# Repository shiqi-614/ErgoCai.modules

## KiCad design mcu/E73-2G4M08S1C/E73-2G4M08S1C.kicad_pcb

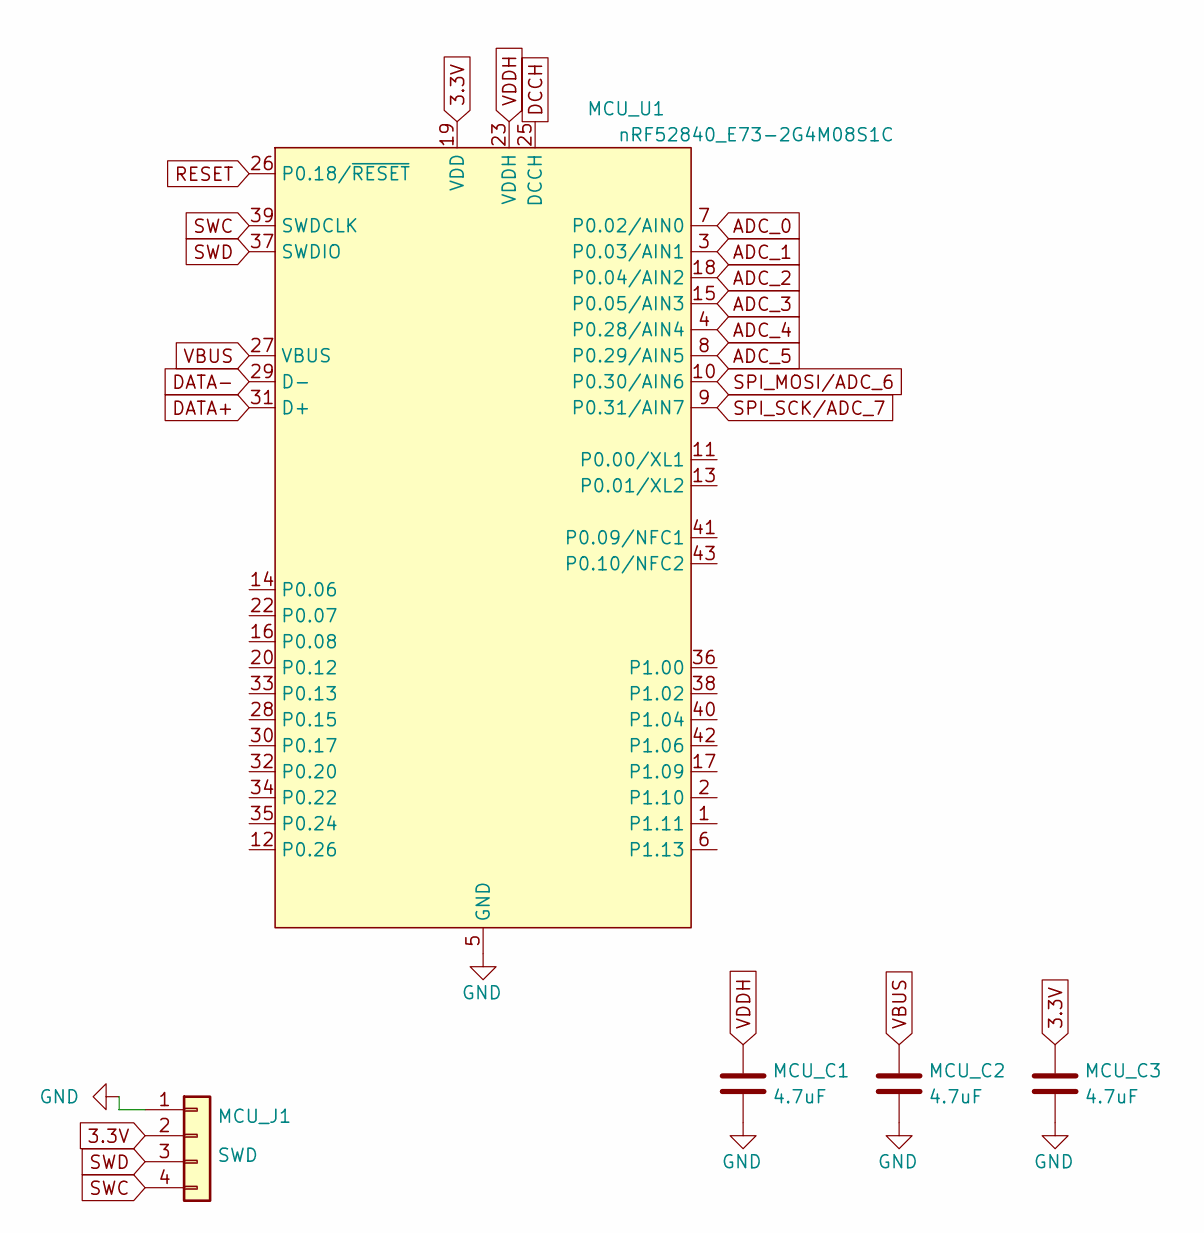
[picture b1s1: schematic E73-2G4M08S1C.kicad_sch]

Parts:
MCU_C1, MCU_C2, MCU_C3: 4.7uF; C_0603_1608Metric
MCU_J1: SWD; Connector_THT_1x4_2.54
MCU_U1: nRF52840_E73-2G4M08S1C; LCSC C356849

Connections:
3.3V: MCU_C3.1, MCU_J1.2, MCU_U1.19 (VDD)
ADC_0: MCU_U1.7 (P0.02/AIN0)
ADC_1: MCU_U1.3 (P0.03/AIN1)
ADC_2: MCU_U1.18 (P0.04/AIN2)
ADC_3: MCU_U1.15 (P0.05/AIN3)
ADC_4: MCU_U1.4 (P0.28/AIN4)
ADC_5: MCU_U1.8 (P0.29/AIN5)
DATA+: MCU_U1.31 (D+)
DATA-: MCU_U1.29 (D-)
DCCH: MCU_U1.25 (DCCH)
GND: MCU_C1.2, MCU_C2.2, MCU_C3.2, MCU_J1.1, MCU_U1.5 (GND), MCU_U1.21 (GND), MCU_U1.24 (GND)
RESET: MCU_U1.26 (P0.18/~RESET)
SPI_MOSI/ADC_6: MCU_U1.10 (P0.30/AIN6)
SPI_SCK/ADC_7: MCU_U1.9 (P0.31/AIN7)
SWC: MCU_J1.4, MCU_U1.39 (SWDCLK)
SWD: MCU_J1.3, MCU_U1.37 (SWDIO)
VBUS: MCU_C2.1, MCU_U1.27 (VBUS)
VDDH: MCU_C1.1, MCU_U1.23 (VDDH)

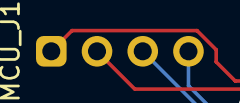
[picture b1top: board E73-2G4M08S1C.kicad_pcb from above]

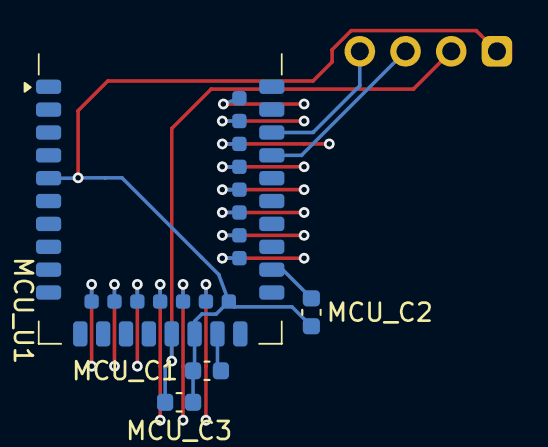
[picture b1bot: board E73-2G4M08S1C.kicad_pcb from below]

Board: 2 copper layers, 5 parts (4 on the bottom side), 6 nets.

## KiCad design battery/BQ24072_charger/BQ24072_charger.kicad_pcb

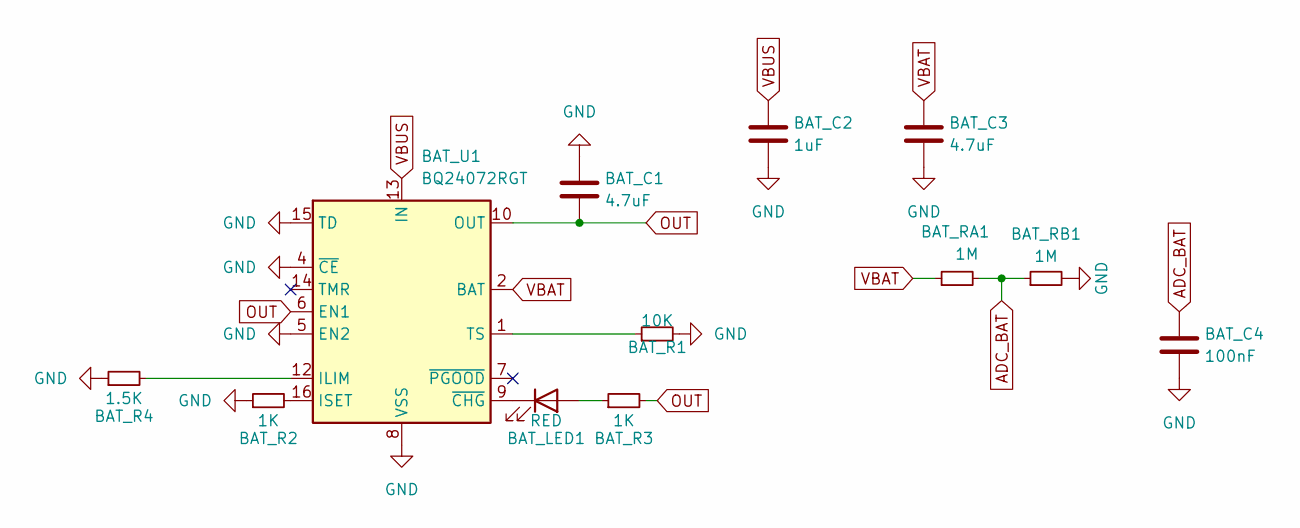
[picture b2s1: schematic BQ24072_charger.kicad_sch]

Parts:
BAT_C1, BAT_C3: 4.7uF; C_0603_1608Metric
BAT_C2: 1uF; C_0603_1608Metric
BAT_C4: 100nF; C_0603_1608Metric
BAT_LED1: RED; LED_0603_1608Metric
BAT_R1: 10K; R_0603_1608Metric
BAT_R2, BAT_R3: 1K; R_0603_1608Metric
BAT_R4: 1.5K; R_0603_1608Metric
BAT_RA1: 1M; R_0603_1608Metric
BAT_RB1: 1M; R_0603_1608Metric
BAT_U1: BQ24072RGT; QFN-16_L3.0-W3.0-P0.50-TL-EP

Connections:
ADC_BAT: BAT_C4.1, BAT_RA1.2, BAT_RB1.1
GND: BAT_C1.1, BAT_C2.2, BAT_C3.2, BAT_C4.2, BAT_R1.2, BAT_R2.1, BAT_R4.1, BAT_RB1.2, BAT_U1.4 (~CE), BAT_U1.5 (EN2), BAT_U1.8 (VSS), BAT_U1.15 (TD), BAT_U1.17 (VSS)
unnamed: BAT_LED1.2 (A), BAT_R3.1
unnamed: BAT_LED1.1 (K), BAT_U1.9 (~CHG)
unnamed: BAT_R4.2, BAT_U1.12 (ILIM)
unnamed: BAT_R2.2, BAT_U1.16 (ISET)
unnamed: BAT_R1.1, BAT_U1.1 (TS)
OUT: BAT_C1.2, BAT_R3.2, BAT_U1.6 (EN1), BAT_U1.10 (OUT), BAT_U1.11 (OUT)
VBAT: BAT_C3.1, BAT_RA1.1, BAT_U1.2 (BAT), BAT_U1.3 (BAT)
VBUS: BAT_C2.1, BAT_U1.13 (IN)

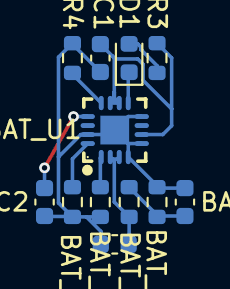
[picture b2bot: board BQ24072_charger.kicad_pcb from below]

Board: 2 copper layers, 12 parts (12 on the bottom side), 10 nets.

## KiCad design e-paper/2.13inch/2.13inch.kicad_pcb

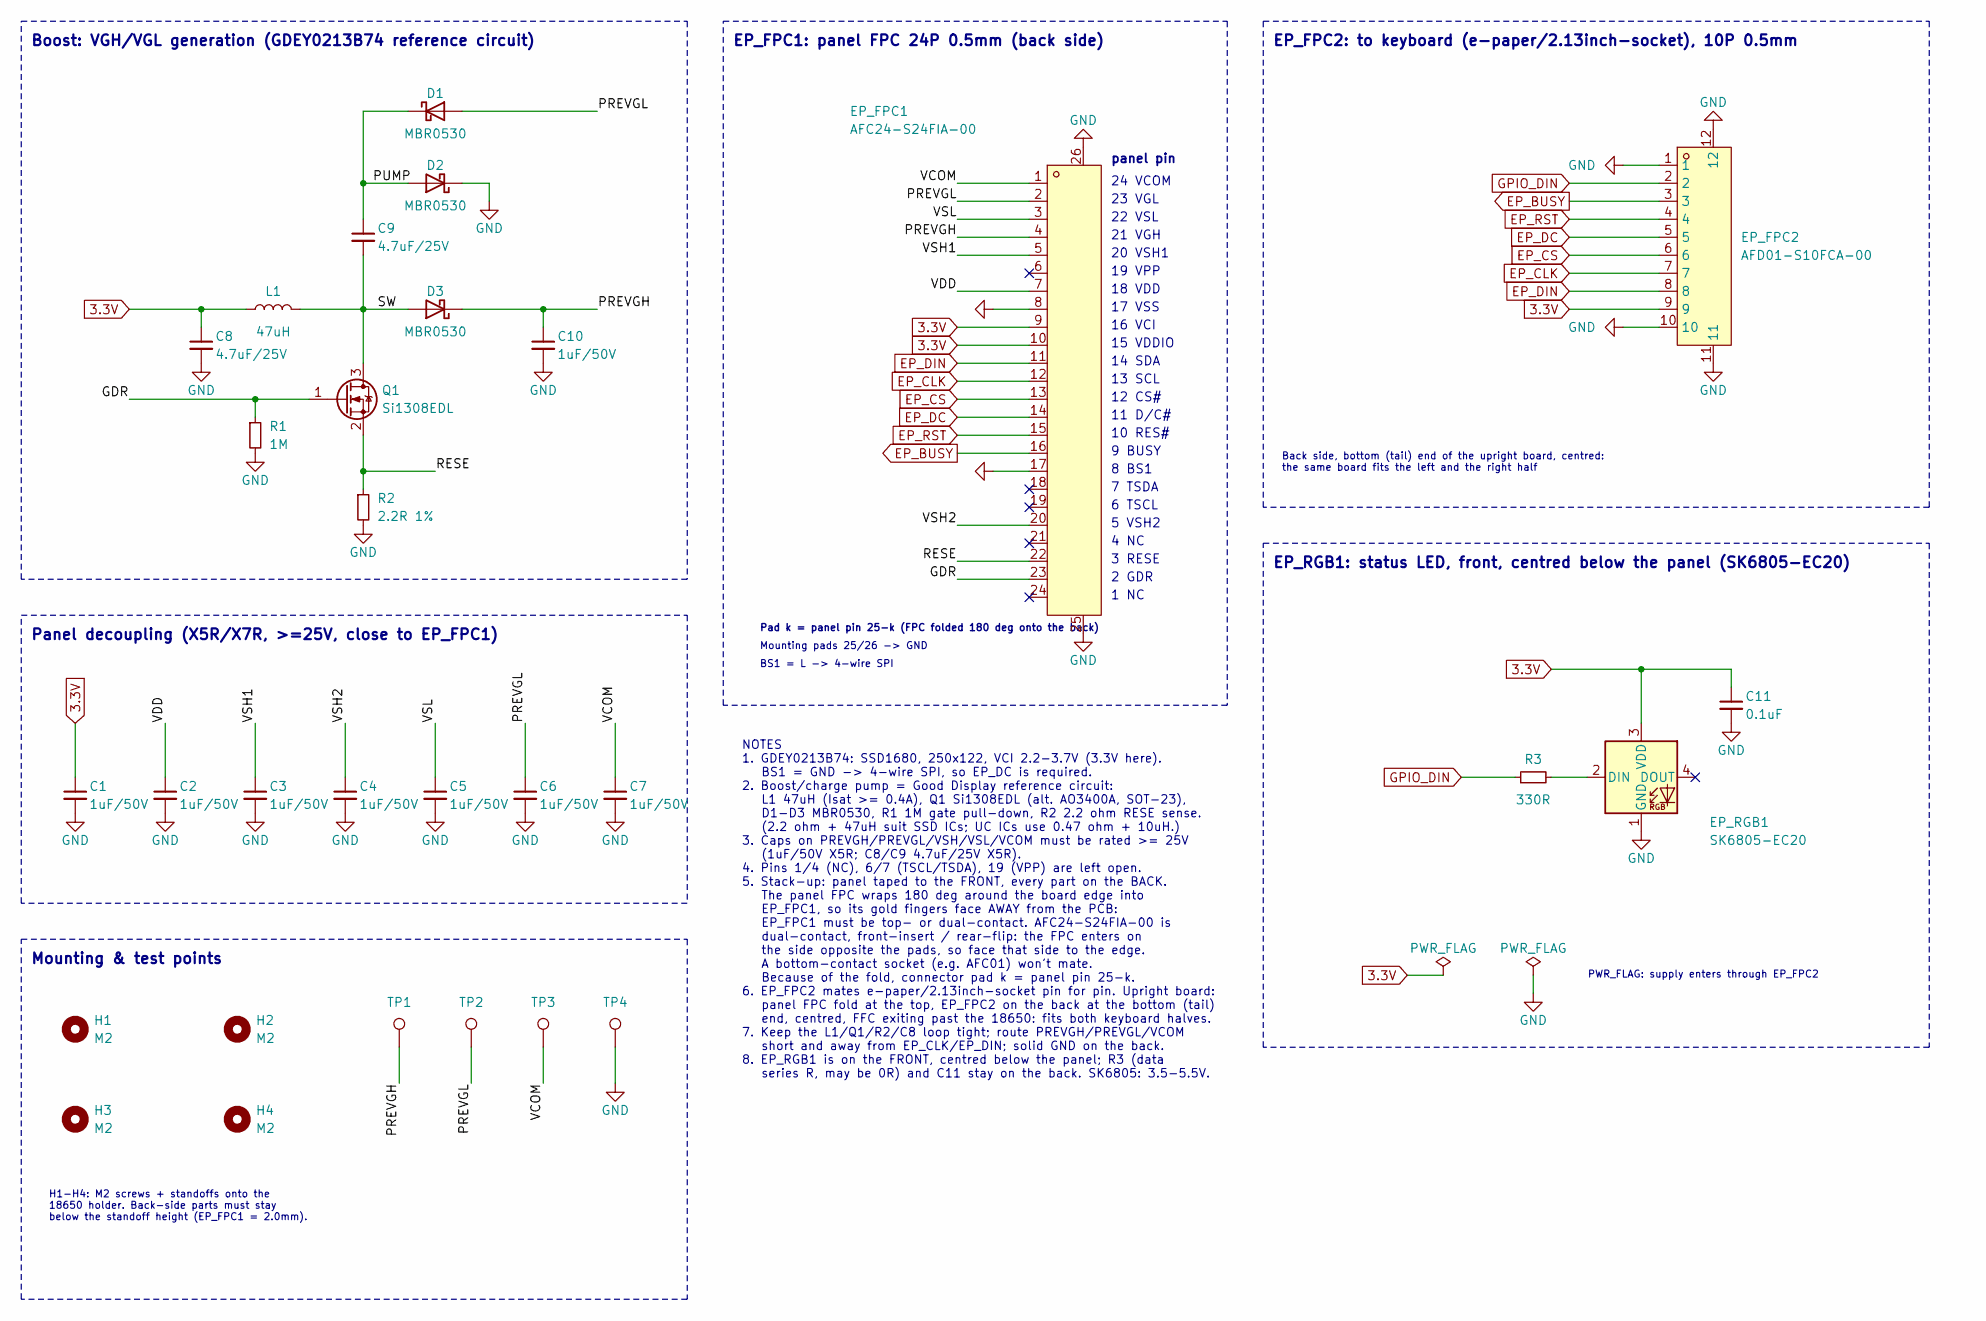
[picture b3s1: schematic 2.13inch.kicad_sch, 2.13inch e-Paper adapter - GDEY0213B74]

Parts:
C1, C2, C3, C4, C5, C6, C7, C10: 1uF/50V; C_0603_1608Metric; LCSC Part C15849
C8, C9: 4.7uF/25V; C_0603_1608Metric; LCSC Part C69335
C11: 0.1uF; C_0603_1608Metric; LCSC Part C14663
D1, D2, D3: MBR0530; D_SOD-123; LCSC Part C82046
EP_FPC1: AFC24-S24FIA-00; FPC-SMD_AFC24-S24FIA-00; LCSC Part C262683
EP_FPC2: AFD01-S10FCA-00; FPC-SMD_10P-P0.50_JS_AFD01-S10FCA-00; LCSC Part C18198578
EP_RGB1: SK6805-EC20; LED_SK6805-EC20_2.0x2.0mm; LCSC Part C2890036
H1, H2, H3, H4: M2; MountingHole_2.2mm_M2_DIN965
L1: 47uH; L_Changjiang_FNR3015S; LCSC Part C167766
Q1: Si1308EDL; SOT-323_SC-70; LCSC Part C469327
R1: 1M; R_0603_1608Metric; LCSC Part C22935
R2: 2.2R 1%; R_0603_1608Metric; LCSC Part C22939
R3: 330R; R_0603_1608Metric; LCSC Part C23138
TP1: PREVGH; TestPoint_Pad_D1.0mm
TP2: PREVGL; TestPoint_Pad_D1.0mm
TP3: VCOM; TestPoint_Pad_D1.0mm
TP4: GND; TestPoint_Pad_D1.0mm

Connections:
3.3V: C1.1, C8.1, C11.1, EP_FPC1.9, EP_FPC1.10, EP_FPC2.9, EP_RGB1.3 (VDD), L1.1
/GDR: EP_FPC1.23, Q1.1 (G), R1.1
/PREVGH: C10.1, D3.1 (K), EP_FPC1.4, TP1.1
/PREVGL: C6.1, D1.2 (A), EP_FPC1.2, TP2.1
/PUMP: C9.1, D1.1 (K), D2.2 (A)
/RESE: EP_FPC1.22, Q1.2 (S), R2.1
/SW: C9.2, D3.2 (A), L1.2, Q1.3 (D)
/VCOM: C7.1, EP_FPC1.1, TP3.1
/VDD: C2.1, EP_FPC1.7
/VSH1: C3.1, EP_FPC1.5
/VSH2: C4.1, EP_FPC1.20
/VSL: C5.1, EP_FPC1.3
EP_BUSY: EP_FPC1.16, EP_FPC2.3
EP_CLK: EP_FPC1.12, EP_FPC2.7
EP_CS: EP_FPC1.13, EP_FPC2.6
EP_DC: EP_FPC1.14, EP_FPC2.5
EP_DIN: EP_FPC1.11, EP_FPC2.8
EP_RST: EP_FPC1.15, EP_FPC2.4
GND: C1.2, C2.2, C3.2, C4.2, C5.2, C6.2, C7.2, C8.2, C10.2, C11.2, D2.1 (K), EP_FPC1.8, EP_FPC1.17, EP_FPC1.25, EP_FPC1.26, EP_FPC2.1, EP_FPC2.10, EP_FPC2.11, EP_FPC2.12, EP_RGB1.1 (GND), R1.2, R2.2, TP4.1
GPIO_DIN: EP_FPC2.2, R3.1
unnamed: EP_RGB1.2 (DIN), R3.2

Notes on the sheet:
Boost: VGH/VGL generation (GDEY0213B74 reference circuit)
Panel decoupling (X5R/X7R, >=25V, close to EP_FPC1)
Mounting & test points
H1-H4: M2 screws + standoffs onto the 18650 holder. Back-side parts must stay below the standoff height (EP_FPC1 = 2.0mm).
EP_FPC1: panel FPC 24P 0.5mm (back side)
panel pin
1 NC
2 GDR
3 RESE
4 NC
5 VSH2
6 TSCL
7 TSDA
8 BS1
9 BUSY
10 RES#
11 D/C#
12 CS#
13 SCL
14 SDA
15 VDDIO
16 VCI
17 VSS
18 VDD
19 VPP
20 VSH1
21 VGH
22 VSL
23 VGL
24 VCOM
Pad k = panel pin 25-k (FPC folded 180 deg onto the back)
Mounting pads 25/26 -> GND
BS1 = L -> 4-wire SPI
EP_FPC2: to keyboard (e-paper/2.13inch-socket), 10P 0.5mm
Back side, bottom (tail) end of the upright board, centred: the same board fits the left and the right half
EP_RGB1: status LED, front, centred below the panel (SK6805-EC20)
PWR_FLAG: supply enters through EP_FPC2
NOTES 1. GDEY0213B74: SSD1680, 250x122, VCI 2.2-3.7V (3.3V here). BS1 = GND -> 4-wire SPI, so EP_DC is required. 2. Boost/charge pump = Good Display reference circuit: L1 47uH (Isat >= 0.4A), Q1 Si1308EDL (alt. AO3400A, SOT-23), D1-D3 MBR0530, R1 1M gate pull-down, R2 2.2 ohm RESE sense. (2.2 ohm +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

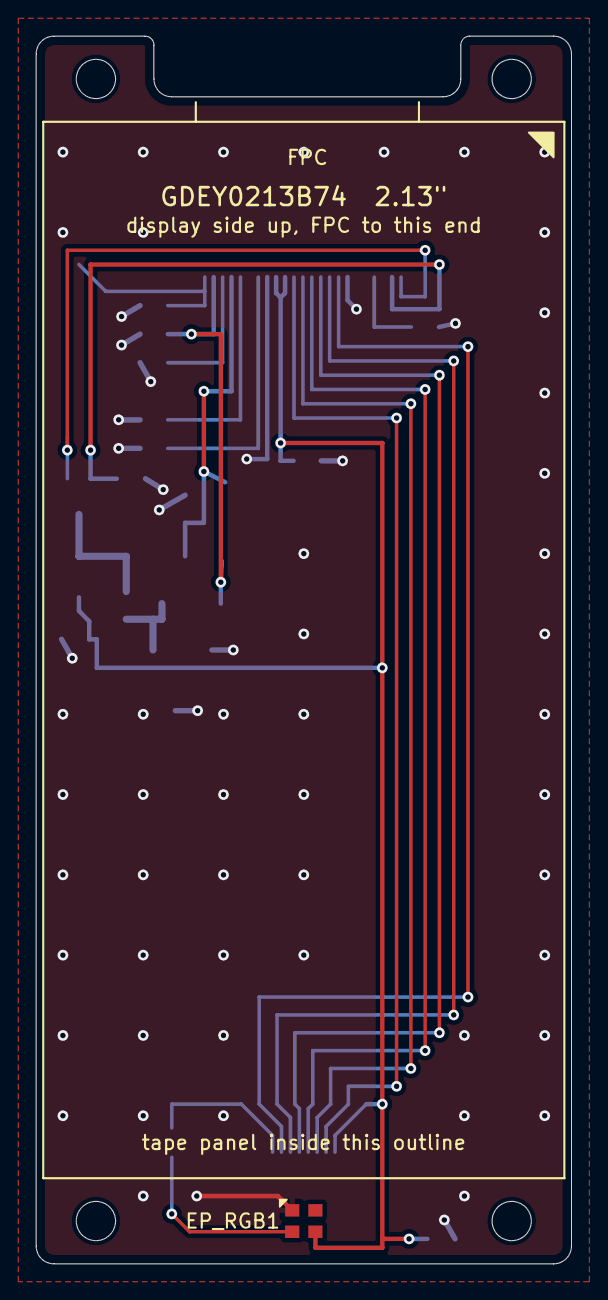
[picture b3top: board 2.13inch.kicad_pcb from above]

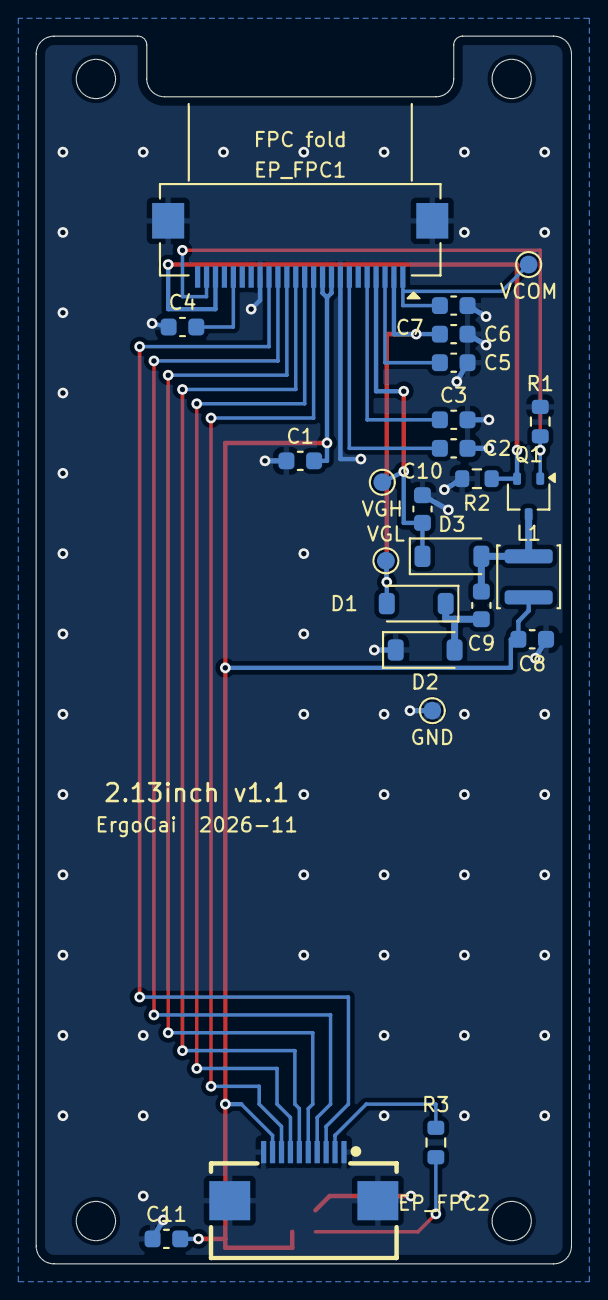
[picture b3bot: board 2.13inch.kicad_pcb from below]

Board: 2 copper layers, 30.0 x 68.8 mm, 30 parts (25 on the bottom side), 21 nets.

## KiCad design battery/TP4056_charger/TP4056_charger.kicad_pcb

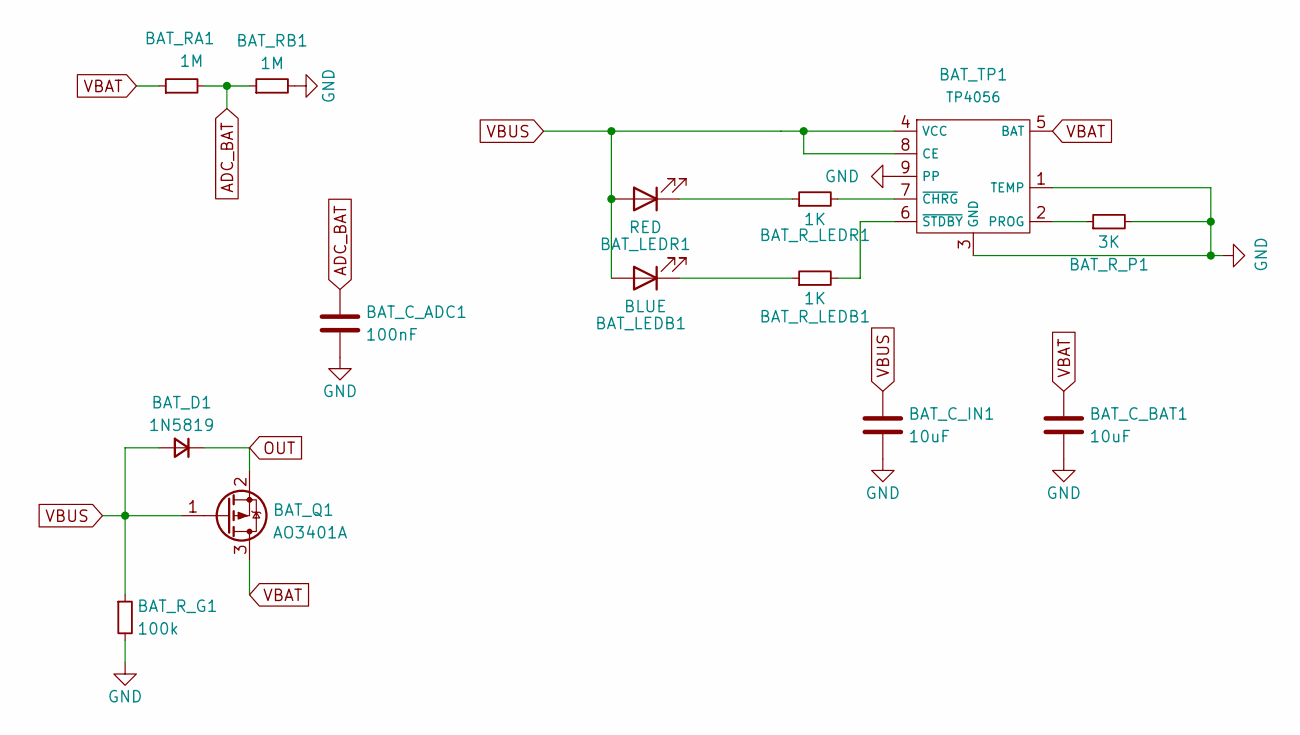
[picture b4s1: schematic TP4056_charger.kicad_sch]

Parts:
BAT_C_ADC1: 100nF; C_0603_1608Metric
BAT_C_BAT1: 10uF; C_0603_1608Metric
BAT_C_IN1: 10uF; C_0603_1608Metric
BAT_D1: 1N5819; D_SOD-123
BAT_LEDB1: BLUE; LED_0603_1608Metric
BAT_LEDR1: RED; LED_0603_1608Metric
BAT_Q1: AO3401A; SOT-23
BAT_RA1: 1M; R_0603_1608Metric
BAT_RB1: 1M; R_0603_1608Metric
BAT_R_G1: 100k; R_0603_1608Metric
BAT_R_LEDB1: 1K; R_0603_1608Metric
BAT_R_LEDR1: 1K; R_0603_1608Metric
BAT_R_P1: 3K; R_0603_1608Metric
BAT_TP1: TP4056; SOIC-8-1EP_3.9x4.9mm_P1.27mm_EP2.29x3mm

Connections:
ADC_BAT: BAT_C_ADC1.1, BAT_RA1.2, BAT_RB1.1
GND: BAT_C_ADC1.2, BAT_C_BAT1.2, BAT_C_IN1.2, BAT_RB1.2, BAT_R_G1.2, BAT_R_P1.2, BAT_TP1.1 (TEMP), BAT_TP1.3 (GND), BAT_TP1.9 (PP)
unnamed: BAT_LEDB1.1 (K), BAT_R_LEDB1.1
unnamed: BAT_LEDR1.1 (K), BAT_R_LEDR1.1
unnamed: BAT_R_P1.1, BAT_TP1.2 (PROG)
unnamed: BAT_R_LEDR1.2, BAT_TP1.7 (~CHRG)
unnamed: BAT_R_LEDB1.2, BAT_TP1.6 (~STDBY)
OUT: BAT_D1.1 (K), BAT_Q1.2 (S)
VBAT: BAT_C_BAT1.1, BAT_Q1.3 (D), BAT_RA1.1, BAT_TP1.5 (BAT)
VBUS: BAT_C_IN1.1, BAT_D1.2 (A), BAT_LEDB1.2 (A), BAT_LEDR1.2 (A), BAT_Q1.1 (G), BAT_R_G1.1, BAT_TP1.4 (VCC), BAT_TP1.8 (CE)

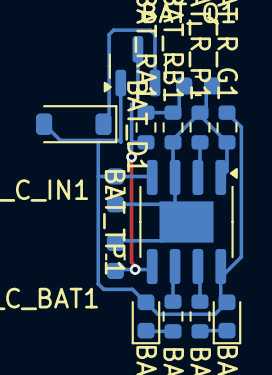
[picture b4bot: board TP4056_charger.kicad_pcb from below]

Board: 2 copper layers, 14 parts (14 on the bottom side), 10 nets.

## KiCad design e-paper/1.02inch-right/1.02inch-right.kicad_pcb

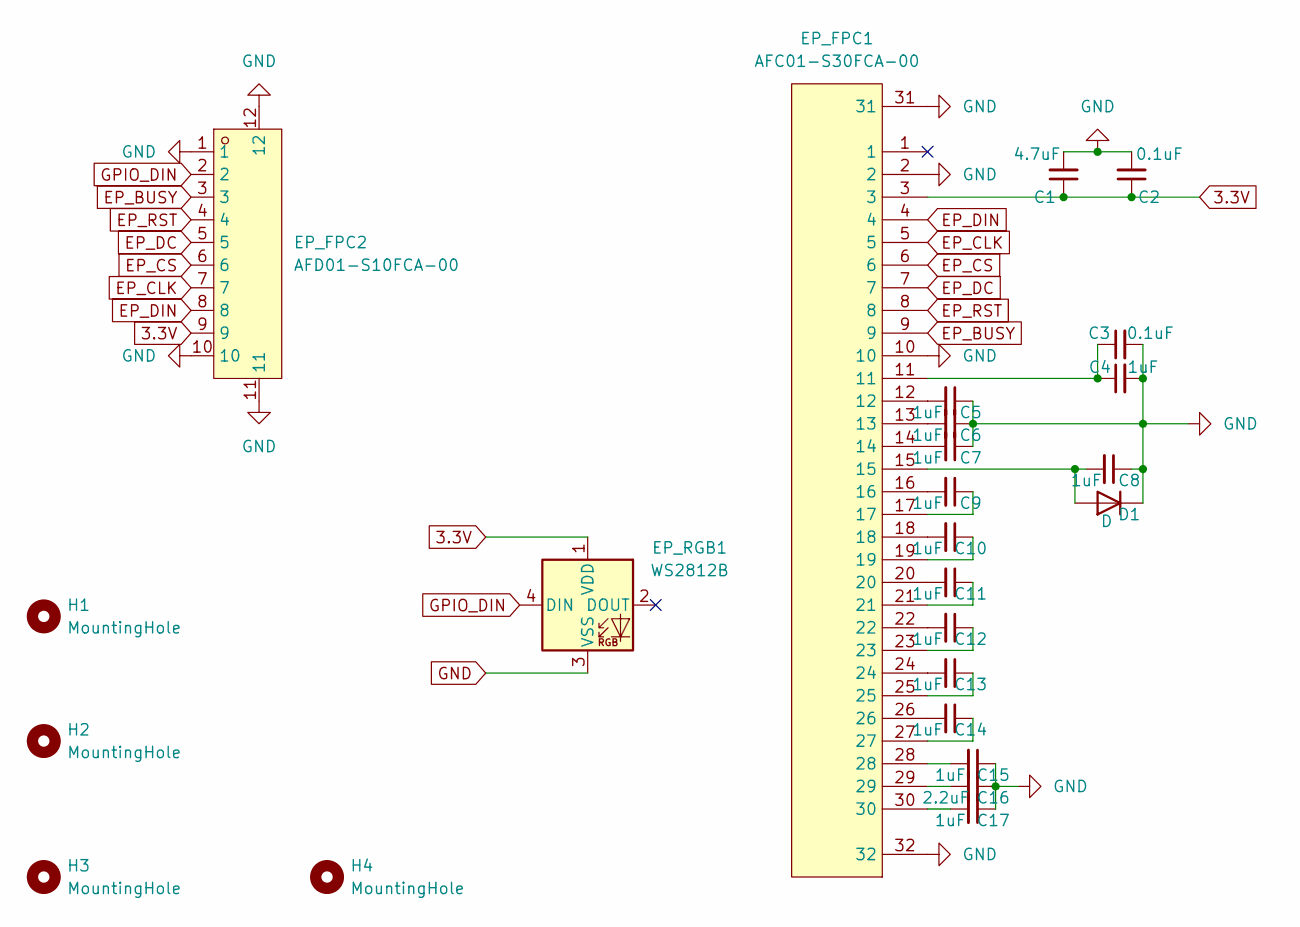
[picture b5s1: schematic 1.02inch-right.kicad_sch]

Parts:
C1: 4.7uF; C_0603_1608Metric
C2, C3: 0.1uF; C_0603_1608Metric
C4, C5, C6, C7, C8, C9, C10, C11, C12, C13, C14, C15, C17: 1uF; C_0603_1608Metric
C16: 2.2uF; C_0603_1608Metric
D1: D; D_SOD-123
EP_FPC1: AFC01-S30FCA-00; FPC-SMD_AFC01-S30FCA-00; LCSC Part C262671
EP_FPC2: AFD01-S10FCA-00; FPC-SMD_10P-P0.50_JS_AFD01-S10FCA-00; LCSC Part C18198578
EP_RGB1: WS2812B; LED_6028R
H1, H2, H3, H4: MountingHole; MountingHole_2.2mm_M2_DIN965

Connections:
3.3V: C1.1, C2.1, EP_FPC1.3, EP_FPC2.9, EP_RGB1.1 (VDD)
EP_BUSY: EP_FPC1.9, EP_FPC2.3
EP_CLK: EP_FPC1.5, EP_FPC2.7
EP_CS: EP_FPC1.6, EP_FPC2.6
EP_DC: EP_FPC1.7, EP_FPC2.5
EP_DIN: EP_FPC1.4, EP_FPC2.8
EP_RST: EP_FPC1.8, EP_FPC2.4
GND: C1.2, C2.2, C3.2, C4.2, C5.1, C6.1, C7.1, C8.1, C15.1, C16.1, C17.1, D1.1 (K), EP_FPC1.2, EP_FPC1.10, EP_FPC1.31, EP_FPC1.32, EP_FPC2.1, EP_FPC2.10, EP_FPC2.11, EP_FPC2.12, EP_RGB1.3 (VSS)
GPIO_DIN: EP_FPC2.2, EP_RGB1.4 (DIN)
unnamed: C3.1, C4.1, EP_FPC1.11
unnamed: C5.2, EP_FPC1.12
unnamed: C6.2, EP_FPC1.13
unnamed: C7.2, EP_FPC1.14
unnamed: C9.1, EP_FPC1.17
unnamed: C9.2, EP_FPC1.16
unnamed: C10.1, EP_FPC1.19
unnamed: C10.2, EP_FPC1.18
unnamed: C11.1, EP_FPC1.21
unnamed: C11.2, EP_FPC1.20
unnamed: C12.1, EP_FPC1.23
unnamed: C12.2, EP_FPC1.22
unnamed: C13.1, EP_FPC1.25
unnamed: C13.2, EP_FPC1.24
unnamed: C14.1, EP_FPC1.27
unnamed: C14.2, EP_FPC1.26
unnamed: C15.2, EP_FPC1.28
unnamed: C16.2, EP_FPC1.29
unnamed: C17.2, EP_FPC1.30
unnamed: C8.2, D1.2 (A), EP_FPC1.15

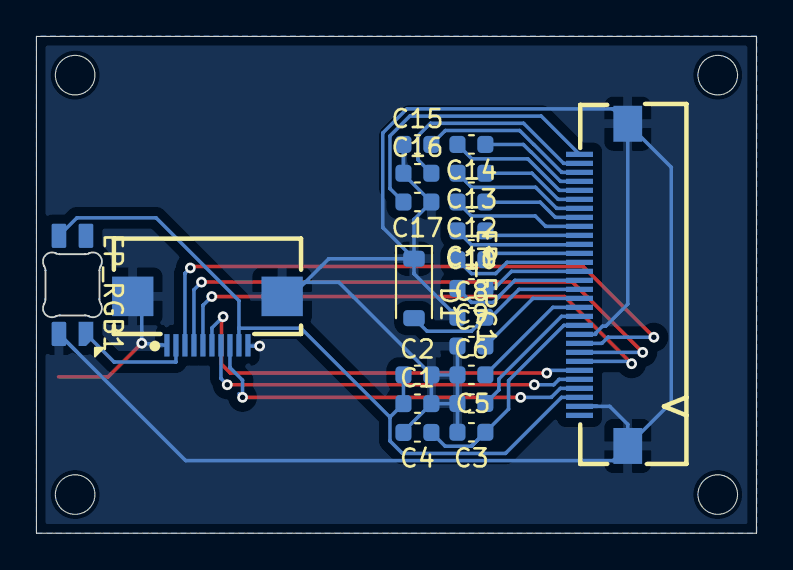
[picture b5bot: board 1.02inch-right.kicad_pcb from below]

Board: 2 copper layers, 39.9 x 27.6 mm, 25 parts (21 on the bottom side), 29 nets.

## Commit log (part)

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2025-02-16 correct template path
2025-02-16 update footprint related posotion in tp4056 and 18650 correct default_18650_AP2112K schematic
2025-02-17 add default usb module
2025-02-17 update CHRG_R_CHRG1 position
2025-02-22 correct default_TP4056.yaml
2025-02-22 add mcu nRF52840_holyiot_18010
2025-02-24 update mcu nRF52840_holyiot_18010 annotation
2025-02-25 correct rotate MCU_SW1
2025-02-25 correct rotate of USB_C1
2025-04-06 change R cc1 cc2 pos
2025-04-06 remove useless reset in nrf52840
2025-04-21 update usb
2025-04-22 remove TP4056 and add it to battery
2025-04-22 correct usb cc1 cc2 rotate
2025-04-22 correct mcu footprint
2025-04-22 update sch files
2025-04-24 correct footprint path, add .pretty update templates
2025-05-31 correct reset button path
2025-06-01 update battery module
2025-06-01 update battery U1 U2 position to ensure annotation order
2025-06-03 upgrade modules with kicad_sh and kicad_pcb
2025-06-03 correct mcu side
2025-06-03 update usb_c template
2025-06-07 remove old yaml template and update default usb pcb
2025-06-17 add track between gnd in mcu
2025-06-22 move mcu to (0, 0)
2025-07-05 use nrf52840 simple
2025-07-14 update battery module, change switch
2025-07-15 update battery module, update via pos
2025-07-15 move tp4056 to front
2025-07-17 mvoe battery led to front
2025-07-17 move capacity to usb back
2025-07-17 correct usb pos
2025-07-17 adjust battery via pos
2025-07-18 replace VDD-nRF to VCC
2025-07-26 add Alpsalpine joystick
2025-07-27 update joystick label to global
2025-08-24 add battery_led_back
2025-08-28 add joystick module
2025-09-02 add joystick mount
2025-09-02 add drawing layer for joystck mount
2025-09-02 update joystick mount footprint
2025-09-06 add RGB WS2812B modules
2025-09-06 update RGB position
2025-09-14 update joystick mount connector to JST ZH
2025-09-15 update joystick mount pos
2025-09-19 use SY8088AAC in battery modules
2025-10-14 update RGB LEB pin name
2025-10-20 add usb gnd connection
2025-11-01 update bat line
2025-11-02 update vbus route
2025-11-02 add connection between reset
2025-11-07 correct battery via connection
2025-11-08 add gnd via in mcu
2025-11-08 add reset module
2025-11-10 add battery_all_back
2025-11-11 update mcu debug port pos
2025-11-16 update battery all back
2025-11-16 update battery switch symbol
2025-11-17 remove default battery
2025-11-17 update mcu j1 pos
2025-11-18 use vcc instead of vin in led
2025-11-26 add power switch
2026-01-19 update to 3.3V tag
2026-01-19 add e-paper
2026-01-19 add tp4056 charger
2026-01-19 add 1 rbg
2026-01-19 update e-paper boundary
2026-01-21 update reference in joystick and e-paper
2026-01-22 update e-paper
2026-01-24 update joystick mount
2026-01-25 add country yard to power swith
2026-01-26 update joystick size
2026-01-31 update footprint in battery switch
2026-01-31 update usb and switch boundry
2026-02-01 add RGB led in e-paper module
2026-02-16 update 3d model pos
2026-02-16 use 10pin connector socket instead of 9
2026-02-16 add holyiot_18010_nRF52840.step
2026-02-16 update K2-1187SQ 3d model
2026-02-16 use SK12D07VG5
2026-02-21 updat e-paper module
2026-02-21 update reset, remove led
2026-02-22 update joystick FPC to 6 pins
2026-03-09 update usb layout
2026-04-06 separate charger and battery
2026-04-14 update e-papert
2026-04-15 add 14500 battery
2026-04-16 remove gnd link in e-paper socket
2026-04-16 add joystick_fpc_hole
2026-04-20 add SWC SWD track in mcu
2026-04-26 correct tracks in e-paper socket
2026-05-04 update via pos in usb
2026-05-04 remove vin in charger
2026-05-10 remove gap between e-paper hole and mount
2026-05-16 update power switch
2026-05-16 correct JST_PH_P2.00mm pos
2026-05-18 update TP4056 charger
